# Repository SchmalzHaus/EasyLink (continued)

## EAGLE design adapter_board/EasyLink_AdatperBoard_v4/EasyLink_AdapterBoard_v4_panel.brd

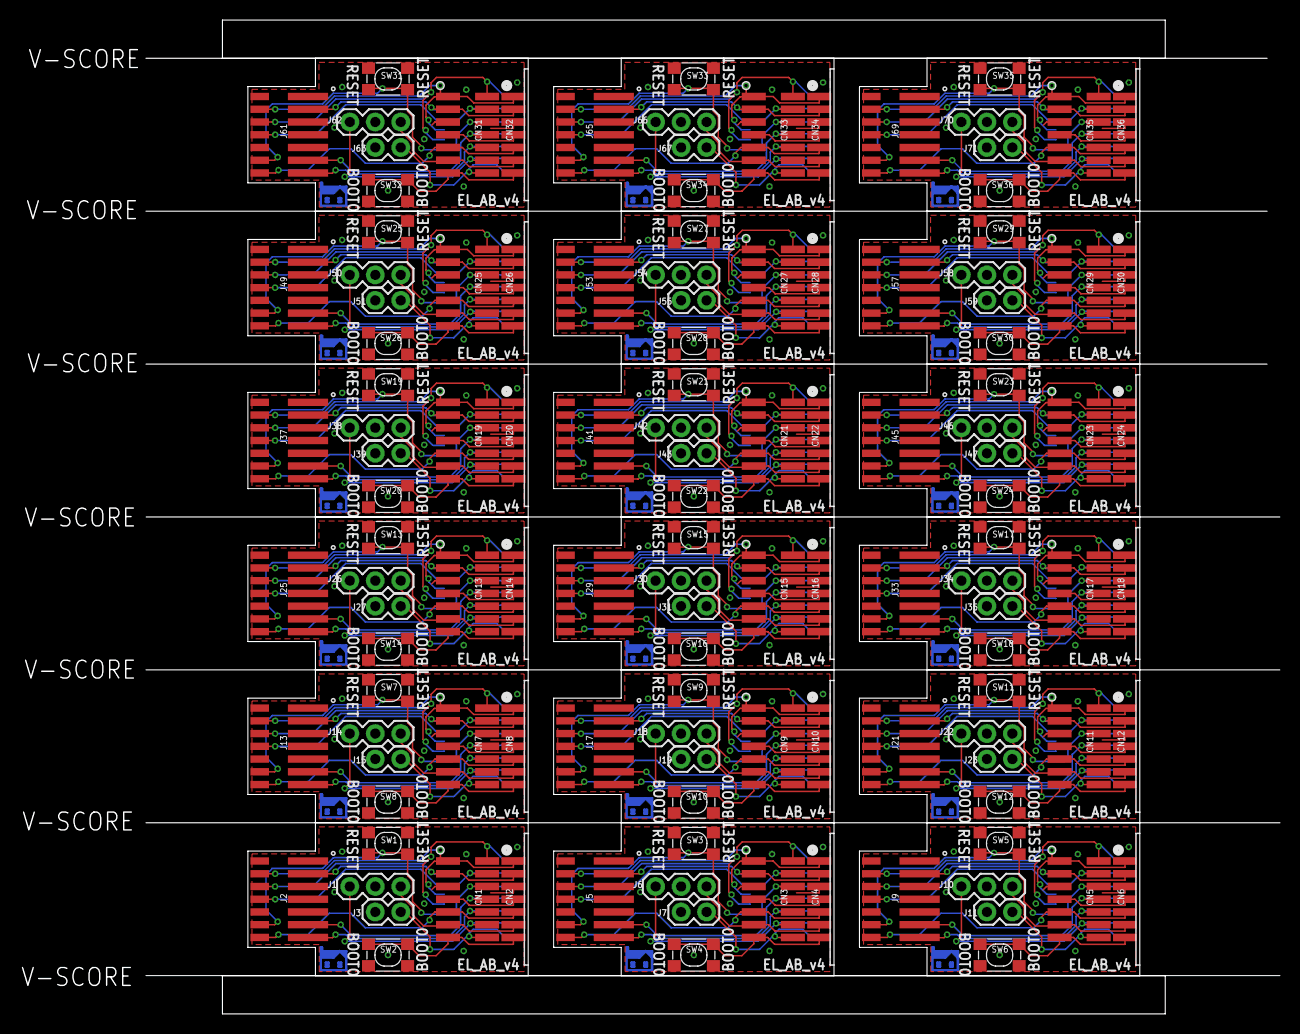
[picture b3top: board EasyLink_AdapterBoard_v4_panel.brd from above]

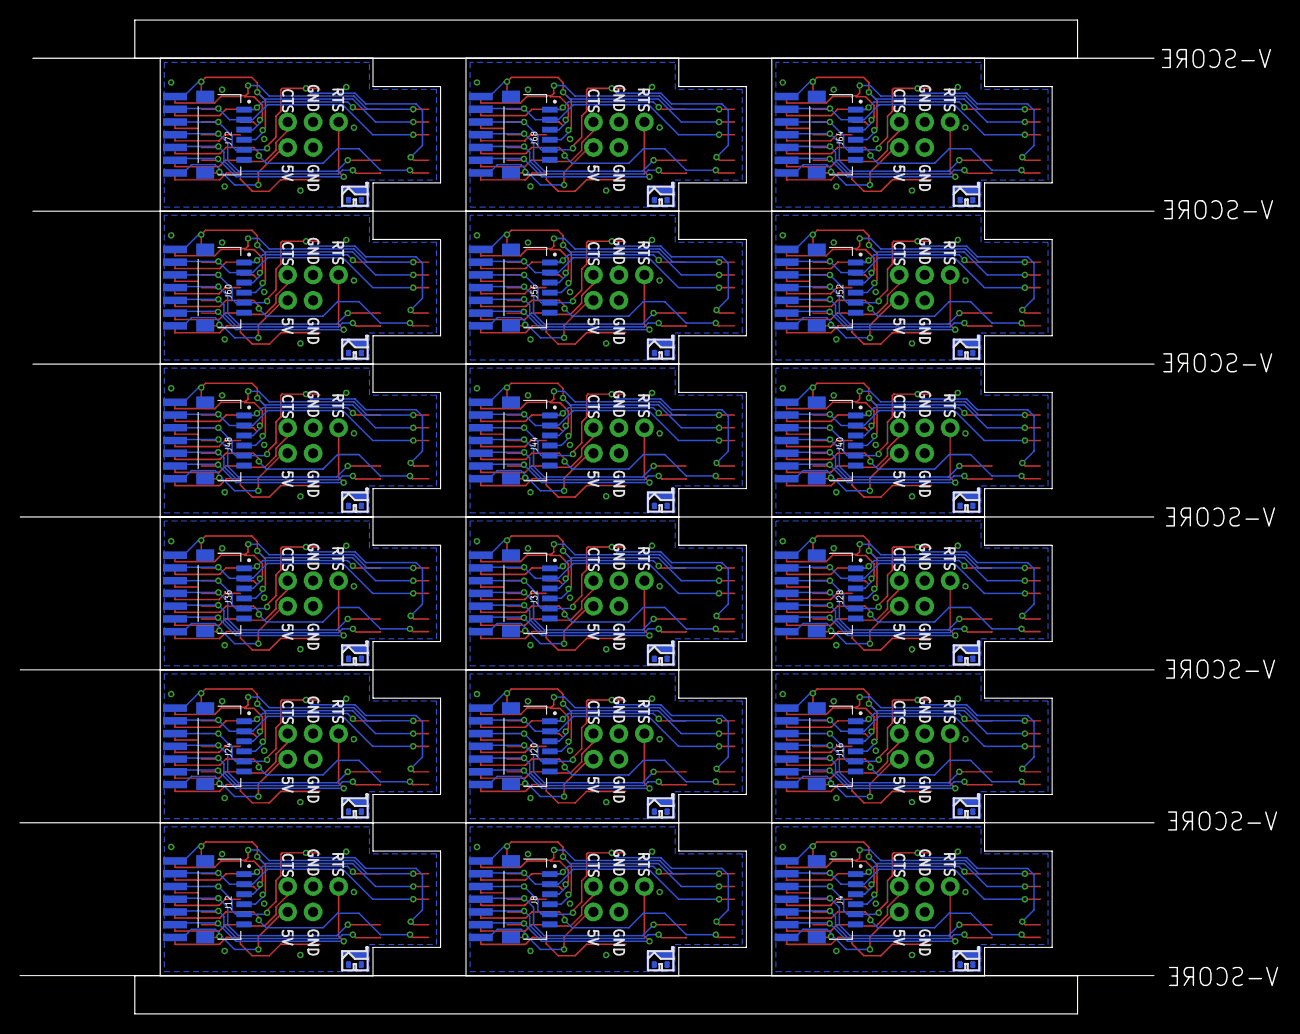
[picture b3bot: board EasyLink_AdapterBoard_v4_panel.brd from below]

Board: 2 copper layers, 113.0 x 99.1 mm, 162 parts (36 on the bottom side), 234 nets.

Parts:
CN1, CN3, CN5, CN7, CN9, CN11, CN13, CN15, CN17, CN19, CN21, CN23, CN25, CN27, CN29, CN31, CN33, CN35: 2X7_DEBUG_HEADFER; 20021121_2X7_SMT_MALE
CN2, CN4, CN6, CN8, CN10, CN12, CN14, CN16, CN18, CN20, CN22, CN24, CN26, CN28, CN30, CN32, CN34, CN36: 2X7_DEBUG_HEADFEREDGE; 2X7_MALE_BOARD_STRADDLE
J1, J6, J10, J14, J18, J22, J26, J30, J34, J38, J42, J46, J50, J54, J58, J62, J66, J70: 1X03
J2, J5, J9, J13, J17, J21, J25, J29, J33, J37, J41, J45, J49, J53, J57, J61, J65, J69: FLE-107-01-XX-DVSTLINK; ST_LINK_V3_DIRECT
J3, J7, J11, J15, J19, J23, J27, J31, J35, J39, J43, J47, J51, J55, J59, J63, J67, J71: 1X02
J4, J8, J12, J16, J20, J24, J28, J32, J36, J40, J44, J48, J52, J56, J60, J64, J68, J72: SM06B-SRSS-TB(LF)(SN); JST_SM06B-SRSS-TB(LF)(SN)
SW1, SW2, SW3, SW4, SW5, SW6, SW7, SW8, SW9, SW10, SW11, SW12, SW13, SW14, SW15, SW16, SW17, SW18, SW19, SW20, SW21, SW22, SW23, SW24, SW25, SW26, SW27, SW28, SW29, SW30, SW31, SW32, SW33, SW34, SW35, SW36: DHT-4235A; SW4-SMD-4.2X3.2X2.5MM
U$1, U$2, U$3, U$4, U$5, U$6, U$7, U$8, U$9, U$10, U$11, U$12, U$13, U$14, U$15, U$16, U$17, U$18: SCHMALZHAUSSCHMALZHAUS_SMALL; SCHMALZHAUS_SMALL

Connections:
3V3_T_VCC: CN1.P$3, CN2.P$3, J2.3, J4.1
3V3_T_VCC1: CN3.P$3, CN4.P$3, J5.3, J8.1
3V3_T_VCC2: CN5.P$3, CN6.P$3, J9.3, J12.1
3V3_T_VCC3: CN7.P$3, CN8.P$3, J13.3, J16.1
3V3_T_VCC4: CN9.P$3, CN10.P$3, J17.3, J20.1
3V3_T_VCC5: CN11.P$3, CN12.P$3, J21.3, J24.1
3V3_T_VCC6: CN13.P$3, CN14.P$3, J25.3, J28.1
3V3_T_VCC7: CN15.P$3, CN16.P$3, J29.3, J32.1
3V3_T_VCC8: CN17.P$3, CN18.P$3, J33.3, J36.1
3V3_T_VCC9: CN19.P$3, CN20.P$3, J37.3, J40.1
3V3_T_VCC10: CN21.P$3, CN22.P$3, J41.3, J44.1
3V3_T_VCC11: CN23.P$3, CN24.P$3, J45.3, J48.1
3V3_T_VCC12: CN25.P$3, CN26.P$3, J49.3, J52.1
3V3_T_VCC13: CN27.P$3, CN28.P$3, J53.3, J56.1
3V3_T_VCC14: CN29.P$3, CN30.P$3, J57.3, J60.1
3V3_T_VCC15: CN31.P$3, CN32.P$3, J61.3, J64.1
3V3_T_VCC16: CN33.P$3, CN34.P$3, J65.3, J68.1
3V3_T_VCC17: CN35.P$3, CN36.P$3, J69.3, J72.1
5V: CN1.P$14, CN2.P$14, J3.1
5V1: CN3.P$14, CN4.P$14, J7.1
5V2: CN5.P$14, CN6.P$14, J11.1
5V3: CN7.P$14, CN8.P$14, J15.1
5V4: CN9.P$14, CN10.P$14, J19.1
5V5: CN11.P$14, CN12.P$14, J23.1
5V6: CN13.P$14, CN14.P$14, J27.1
5V7: CN15.P$14, CN16.P$14, J31.1
5V8: CN17.P$14, CN18.P$14, J35.1
5V9: CN19.P$14, CN20.P$14, J39.1
5V10: CN21.P$14, CN22.P$14, J43.1
5V11: CN23.P$14, CN24.P$14, J47.1
5V12: CN25.P$14, CN26.P$14, J51.1
5V13: CN27.P$14, CN28.P$14, J55.1
5V14: CN29.P$14, CN30.P$14, J59.1
5V15: CN31.P$14, CN32.P$14, J63.1
5V16: CN33.P$14, CN34.P$14, J67.1
5V17: CN35.P$14, CN36.P$14, J71.1
BOOT0: CN1.P$13, CN2.P$13, SW2.1, SW2.2
BOOT1: CN3.P$13, CN4.P$13, SW4.1, SW4.2
BOOT2: CN5.P$13, CN6.P$13, SW6.1, SW6.2
BOOT3: CN7.P$13, CN8.P$13, SW8.1, SW8.2
BOOT4: CN9.P$13, CN10.P$13, SW10.1, SW10.2
BOOT5: CN11.P$13, CN12.P$13, SW12.1, SW12.2
BOOT6: CN13.P$13, CN14.P$13, SW14.1, SW14.2
BOOT7: CN15.P$13, CN16.P$13, SW16.1, SW16.2
BOOT8: CN17.P$13, CN18.P$13, SW18.1, SW18.2
BOOT9: CN19.P$13, CN20.P$13, SW20.1, SW20.2
BOOT10: CN21.P$13, CN22.P$13, SW22.1, SW22.2
BOOT11: CN23.P$13, CN24.P$13, SW24.1, SW24.2
BOOT12: CN25.P$13, CN26.P$13, SW26.1, SW26.2
BOOT13: CN27.P$13, CN28.P$13, SW28.1, SW28.2
BOOT14: CN29.P$13, CN30.P$13, SW30.1, SW30.2
BOOT15: CN31.P$13, CN32.P$13, SW32.1, SW32.2
BOOT16: CN33.P$13, CN34.P$13, SW34.1, SW34.2
BOOT17: CN35.P$13, CN36.P$13, SW36.1, SW36.2
CTS: CN1.P$11, CN2.P$11, J1.3
CTS1: CN3.P$11, CN4.P$11, J6.3
CTS2: CN5.P$11, CN6.P$11, J10.3
CTS3: CN7.P$11, CN8.P$11, J14.3
CTS4: CN9.P$11, CN10.P$11, J18.3
CTS5: CN11.P$11, CN12.P$11, J22.3
CTS6: CN13.P$11, CN14.P$11, J26.3
CTS7: CN15.P$11, CN16.P$11, J30.3
CTS8: CN17.P$11, CN18.P$11, J34.3
CTS9: CN19.P$11, CN20.P$11, J38.3
CTS10: CN21.P$11, CN22.P$11, J42.3
CTS11: CN23.P$11, CN24.P$11, J46.3
CTS12: CN25.P$11, CN26.P$11, J50.3
CTS13: CN27.P$11, CN28.P$11, J54.3
CTS14: CN29.P$11, CN30.P$11, J58.3
CTS15: CN31.P$11, CN32.P$11, J62.3
CTS16: CN33.P$11, CN34.P$11, J66.3
CTS17: CN35.P$11, CN36.P$11, J70.3
GND: CN1.P$5, CN1.P$7, CN2.P$5, CN2.P$7, J1.2, J2.5, J2.7, J3.2, J4.6, J4.S1, J4.S2, SW1.3, SW1.4, SW2.3, SW2.4
GND1: CN3.P$5, CN3.P$7, CN4.P$5, CN4.P$7, J5.5, J5.7, J6.2, J7.2, J8.6, J8.S1, J8.S2, SW3.3, SW3.4, SW4.3, SW4.4
GND2: CN5.P$5, CN5.P$7, CN6.P$5, CN6.P$7, J9.5, J9.7, J10.2, J11.2, J12.6, J12.S1, J12.S2, SW5.3, SW5.4, SW6.3, SW6.4
GND3: CN7.P$5, CN7.P$7, CN8.P$5, CN8.P$7, J13.5, J13.7, J14.2, J15.2, J16.6, J16.S1, J16.S2, SW7.3, SW7.4, SW8.3, SW8.4
GND4: CN9.P$5, CN9.P$7, CN10.P$5, CN10.P$7, J17.5, J17.7, J18.2, J19.2, J20.6, J20.S1, J20.S2, SW9.3, SW9.4, SW10.3, SW10.4
GND5: CN11.P$5, CN11.P$7, CN12.P$5, CN12.P$7, J21.5, J21.7, J22.2, J23.2, J24.6, J24.S1, J24.S2, SW11.3, SW11.4, SW12.3, SW12.4
GND6: CN13.P$5, CN13.P$7, CN14.P$5, CN14.P$7, J25.5, J25.7, J26.2, J27.2, J28.6, J28.S1, J28.S2, SW13.3, SW13.4, SW14.3, SW14.4
GND7: CN15.P$5, CN15.P$7, CN16.P$5, CN16.P$7, J29.5, J29.7, J30.2, J31.2, J32.6, J32.S1, J32.S2, SW15.3, SW15.4, SW16.3, SW16.4
GND8: CN17.P$5, CN17.P$7, CN18.P$5, CN18.P$7, J33.5, J33.7, J34.2, J35.2, J36.6, J36.S1, J36.S2, SW17.3, SW17.4, SW18.3, SW18.4
GND9: CN19.P$5, CN19.P$7, CN20.P$5, CN20.P$7, J37.5, J37.7, J38.2, J39.2, J40.6, J40.S1, J40.S2, SW19.3, SW19.4, SW20.3, SW20.4
GND10: CN21.P$5, CN21.P$7, CN22.P$5, CN22.P$7, J41.5, J41.7, J42.2, J43.2, J44.6, J44.S1, J44.S2, SW21.3, SW21.4, SW22.3, SW22.4
GND11: CN23.P$5, CN23.P$7, CN24.P$5, CN24.P$7, J45.5, J45.7, J46.2, J47.2, J48.6, J48.S1, J48.S2, SW23.3, SW23.4, SW24.3, SW24.4
GND12: CN25.P$5, CN25.P$7, CN26.P$5, CN26.P$7, J49.5, J49.7, J50.2, J51.2, J52.6, J52.S1, J52.S2, SW25.3, SW25.4, SW26.3, SW26.4
GND13: CN27.P$5, CN27.P$7, CN28.P$5, CN28.P$7, J53.5, J53.7, J54.2, J55.2, J56.6, J56.S1, J56.S2, SW27.3, SW27.4, SW28.3, SW28.4
GND14: CN29.P$5, CN29.P$7, CN30.P$5, CN30.P$7, J57.5, J57.7, J58.2, J59.2, J60.6, J60.S1, J60.S2, SW29.3, SW29.4, SW30.3, SW30.4
GND15: CN31.P$5, CN31.P$7, CN32.P$5, CN32.P$7, J61.5, J61.7, J62.2, J63.2, J64.6, J64.S1, J64.S2, SW31.3, SW31.4, SW32.3, SW32.4
GND16: CN33.P$5, CN33.P$7, CN34.P$5, CN34.P$7, J65.5, J65.7, J66.2, J67.2, J68.6, J68.S1, J68.S2, SW33.3, SW33.4, SW34.3, SW34.4
GND17: CN35.P$5, CN35.P$7, CN36.P$5, CN36.P$7, J69.5, J69.7, J70.2, J71.2, J72.6, J72.S1, J72.S2, SW35.3, SW35.4, SW36.3, SW36.4
NRST: CN1.P$6, CN2.P$6, J2.12, J4.5, SW1.1, SW1.2
NRST1: CN3.P$6, CN4.P$6, J5.12, J8.5, SW3.1, SW3.2
NRST2: CN5.P$6, CN6.P$6, J9.12, J12.5, SW5.1, SW5.2
NRST3: CN7.P$6, CN8.P$6, J13.12, J16.5, SW7.1, SW7.2
NRST4: CN9.P$6, CN10.P$6, J17.12, J20.5, SW9.1, SW9.2
NRST5: CN11.P$6, CN12.P$6, J21.12, J24.5, SW11.1, SW11.2
NRST6: CN13.P$6, CN14.P$6, J25.12, J28.5, SW13.1, SW13.2
NRST7: CN15.P$6, CN16.P$6, J29.12, J32.5, SW15.1, SW15.2
NRST8: CN17.P$6, CN18.P$6, J33.12, J36.5, SW17.1, SW17.2
NRST9: CN19.P$6, CN20.P$6, J37.12, J40.5, SW19.1, SW19.2
NRST10: CN21.P$6, CN22.P$6, J41.12, J44.5, SW21.1, SW21.2
NRST11: CN23.P$6, CN24.P$6, J45.12, J48.5, SW23.1, SW23.2
NRST12: CN25.P$6, CN26.P$6, J49.12, J52.5, SW25.1, SW25.2
NRST13: CN27.P$6, CN28.P$6, J53.12, J56.5, SW27.1, SW27.2
NRST14: CN29.P$6, CN30.P$6, J57.12, J60.5, SW29.1, SW29.2
NRST15: CN31.P$6, CN32.P$6, J61.12, J64.5, SW31.1, SW31.2
NRST16: CN33.P$6, CN34.P$6, J65.12, J68.5, SW33.1, SW33.2
NRST17: CN35.P$6, CN36.P$6, J69.12, J72.5, SW35.1, SW35.2
RTS: CN1.P$12, CN2.P$12, J1.1
RTS1: CN3.P$12, CN4.P$12, J6.1
RTS2: CN5.P$12, CN6.P$12, J10.1
RTS3: CN7.P$12, CN8.P$12, J14.1
RTS4: CN9.P$12, CN10.P$12, J18.1
RTS5: CN11.P$12, CN12.P$12, J22.1
RTS6: CN13.P$12, CN14.P$12, J26.1
RTS7: CN15.P$12, CN16.P$12, J30.1
RTS8: CN17.P$12, CN18.P$12, J34.1
RTS9: CN19.P$12, CN20.P$12, J38.1
RTS10: CN21.P$12, CN22.P$12, J42.1
RTS11: CN23.P$12, CN24.P$12, J46.1
RTS12: CN25.P$12, CN26.P$12, J50.1
RTS13: CN27.P$12, CN28.P$12, J54.1
RTS14: CN29.P$12, CN30.P$12, J58.1
RTS15: CN31.P$12, CN32.P$12, J62.1
RTS16: CN33.P$12, CN34.P$12, J66.1
RTS17: CN35.P$12, CN36.P$12, J70.1
SWCLK: CN1.P$2, CN2.P$2, J2.6, J4.4
SWCLK1: CN3.P$2, CN4.P$2, J5.6, J8.4
SWCLK2: CN5.P$2, CN6.P$2, J9.6, J12.4
SWCLK3: CN7.P$2, CN8.P$2, J13.6, J16.4
SWCLK4: CN9.P$2, CN10.P$2, J17.6, J20.4
SWCLK5: CN11.P$2, CN12.P$2, J21.6, J24.4
SWCLK6: CN13.P$2, CN14.P$2, J25.6, J28.4
SWCLK7: CN15.P$2, CN16.P$2, J29.6, J32.4
SWCLK8: CN17.P$2, CN18.P$2, J33.6, J36.4
SWCLK9: CN19.P$2, CN20.P$2, J37.6, J40.4
SWCLK10: CN21.P$2, CN22.P$2, J41.6, J44.4
SWCLK11: CN23.P$2, CN24.P$2, J45.6, J48.4
SWCLK12: CN25.P$2, CN26.P$2, J49.6, J52.4
SWCLK13: CN27.P$2, CN28.P$2, J53.6, J56.4
SWCLK14: CN29.P$2, CN30.P$2, J57.6, J60.4
SWCLK15: CN31.P$2, CN32.P$2, J61.6, J64.4
SWCLK16: CN33.P$2, CN34.P$2, J65.6, J68.4
SWCLK17: CN35.P$2, CN36.P$2, J69.6, J72.4
SWDIO: CN1.P$1, CN2.P$1, J2.4, J4.3
SWDIO1: CN3.P$1, CN4.P$1, J5.4, J8.3
SWDIO2: CN5.P$1, CN6.P$1, J9.4, J12.3
SWDIO3: CN7.P$1, CN8.P$1, J13.4, J16.3
SWDIO4: CN9.P$1, CN10.P$1, J17.4, J20.3
SWDIO5: CN11.P$1, CN12.P$1, J21.4, J24.3
SWDIO6: CN13.P$1, CN14.P$1, J25.4, J28.3
SWDIO7: CN15.P$1, CN16.P$1, J29.4, J32.3
SWDIO8: CN17.P$1, CN18.P$1, J33.4, J36.3
SWDIO9: CN19.P$1, CN20.P$1, J37.4, J40.3
SWDIO10: CN21.P$1, CN22.P$1, J41.4, J44.3
SWDIO11: CN23.P$1, CN24.P$1, J45.4, J48.3
SWDIO12: CN25.P$1, CN26.P$1, J49.4, J52.3
SWDIO13: CN27.P$1, CN28.P$1, J53.4, J56.3
SWDIO14: CN29.P$1, CN30.P$1, J57.4, J60.3
SWDIO15: CN31.P$1, CN32.P$1, J61.4, J64.3
SWDIO16: CN33.P$1, CN34.P$1, J65.4, J68.3
SWDIO17: CN35.P$1, CN36.P$1, J69.4, J72.3
SWO: CN1.P$4, CN2.P$4, J2.8, J4.2
SWO1: CN3.P$4, CN4.P$4, J5.8, J8.2
SWO2: CN5.P$4, CN6.P$4, J9.8, J12.2
SWO3: CN7.P$4, CN8.P$4, J13.8, J16.2
SWO4: CN9.P$4, CN10.P$4, J17.8, J20.2
SWO5: CN11.P$4, CN12.P$4, J21.8, J24.2
SWO6: CN13.P$4, CN14.P$4, J25.8, J28.2
SWO7: CN15.P$4, CN16.P$4, J29.8, J32.2
SWO8: CN17.P$4, CN18.P$4, J33.8, J36.2
SWO9: CN19.P$4, CN20.P$4, J37.8, J40.2
SWO10: CN21.P$4, CN22.P$4, J41.8, J44.2
SWO11: CN23.P$4, CN24.P$4, J45.8, J48.2
SWO12: CN25.P$4, CN26.P$4, J49.8, J52.2
SWO13: CN27.P$4, CN28.P$4, J53.8, J56.2
SWO14: CN29.P$4, CN30.P$4, J57.8, J60.2
SWO15: CN31.P$4, CN32.P$4, J61.8, J64.2
SWO16: CN33.P$4, CN34.P$4, J65.8, J68.2
SWO17: CN35.P$4, CN36.P$4, J69.8, J72.2
T_GND: CN1.P$8, CN2.P$8, J2.11
T_GND1: CN3.P$8, CN4.P$8, J5.11
T_GND2: CN5.P$8, CN6.P$8, J9.11
T_GND3: CN7.P$8, CN8.P$8, J13.11
T_GND4: CN9.P$8, CN10.P$8, J17.11
T_GND5: CN11.P$8, CN12.P$8, J21.11
T_GND6: CN13.P$8, CN14.P$8, J25.11
T_GND7: CN15.P$8, CN16.P$8, J29.11
T_GND8: CN17.P$8, CN18.P$8, J33.11
T_GND9: CN19.P$8, CN20.P$8, J37.11
T_GND10: CN21.P$8, CN22.P$8, J41.11
T_GND11: CN23.P$8, CN24.P$8, J45.11
T_GND12: CN25.P$8, CN26.P$8, J49.11
T_GND13: CN27.P$8, CN28.P$8, J53.11
T_GND14: CN29.P$8, CN30.P$8, J57.11
T_GND15: CN31.P$8, CN32.P$8, J61.11
T_GND16: CN33.P$8, CN34.P$8, J65.11
T_GND17: CN35.P$8, CN36.P$8, J69.11
VCP_RX_T_TX: CN1.P$9, CN2.P$9, J2.14
VCP_RX_T_TX1: CN3.P$9, CN4.P$9, J5.14
VCP_RX_T_TX2: CN5.P$9, CN6.P$9, J9.14
VCP_RX_T_TX3: CN7.P$9, CN8.P$9, J13.14
VCP_RX_T_TX4: CN9.P$9, CN10.P$9, J17.14
VCP_RX_T_TX5: CN11.P$9, CN12.P$9, J21.14
VCP_RX_T_TX6: CN13.P$9, CN14.P$9, J25.14
VCP_RX_T_TX7: CN15.P$9, CN16.P$9, J29.14
VCP_RX_T_TX8: CN17.P$9, CN18.P$9, J33.14
VCP_RX_T_TX9: CN19.P$9, CN20.P$9, J37.14
VCP_RX_T_TX10: CN21.P$9, CN22.P$9, J41.14
VCP_RX_T_TX11: CN23.P$9, CN24.P$9, J45.14
VCP_RX_T_TX12: CN25.P$9, CN26.P$9, J49.14
VCP_RX_T_TX13: CN27.P$9, CN28.P$9, J53.14
VCP_RX_T_TX14: CN29.P$9, CN30.P$9, J57.14
VCP_RX_T_TX15: CN31.P$9, CN32.P$9, J61.14
VCP_RX_T_TX16: CN33.P$9, CN34.P$9, J65.14
VCP_RX_T_TX17: CN35.P$9, CN36.P$9, J69.14
VCP_TX_T_RX: CN1.P$10, CN2.P$10, J2.13
VCP_TX_T_RX1: CN3.P$10, CN4.P$10, J5.13
VCP_TX_T_RX2: CN5.P$10, CN6.P$10, J9.13
VCP_TX_T_RX3: CN7.P$10, CN8.P$10, J13.13
VCP_TX_T_RX4: CN9.P$10, CN10.P$10, J17.13
VCP_TX_T_RX5: CN11.P$10, CN12.P$10, J21.13
VCP_TX_T_RX6: CN13.P$10, CN14.P$10, J25.13
VCP_TX_T_RX7: CN15.P$10, CN16.P$10, J29.13
VCP_TX_T_RX8: CN17.P$10, CN18.P$10, J33.13
VCP_TX_T_RX9: CN19.P$10, CN20.P$10, J37.13
VCP_TX_T_RX10: CN21.P$10, CN22.P$10, J41.13
VCP_TX_T_RX11: CN23.P$10, CN24.P$10, J45.13
VCP_TX_T_RX12: CN25.P$10, CN26.P$10, J49.13
VCP_TX_T_RX13: CN27.P$10, CN28.P$10, J53.13
VCP_TX_T_RX14: CN29.P$10, CN30.P$10, J57.13
VCP_TX_T_RX15: CN31.P$10, CN32.P$10, J61.13
VCP_TX_T_RX16: CN33.P$10, CN34.P$10, J65.13
VCP_TX_T_RX17: CN35.P$10, CN36.P$10, J69.13

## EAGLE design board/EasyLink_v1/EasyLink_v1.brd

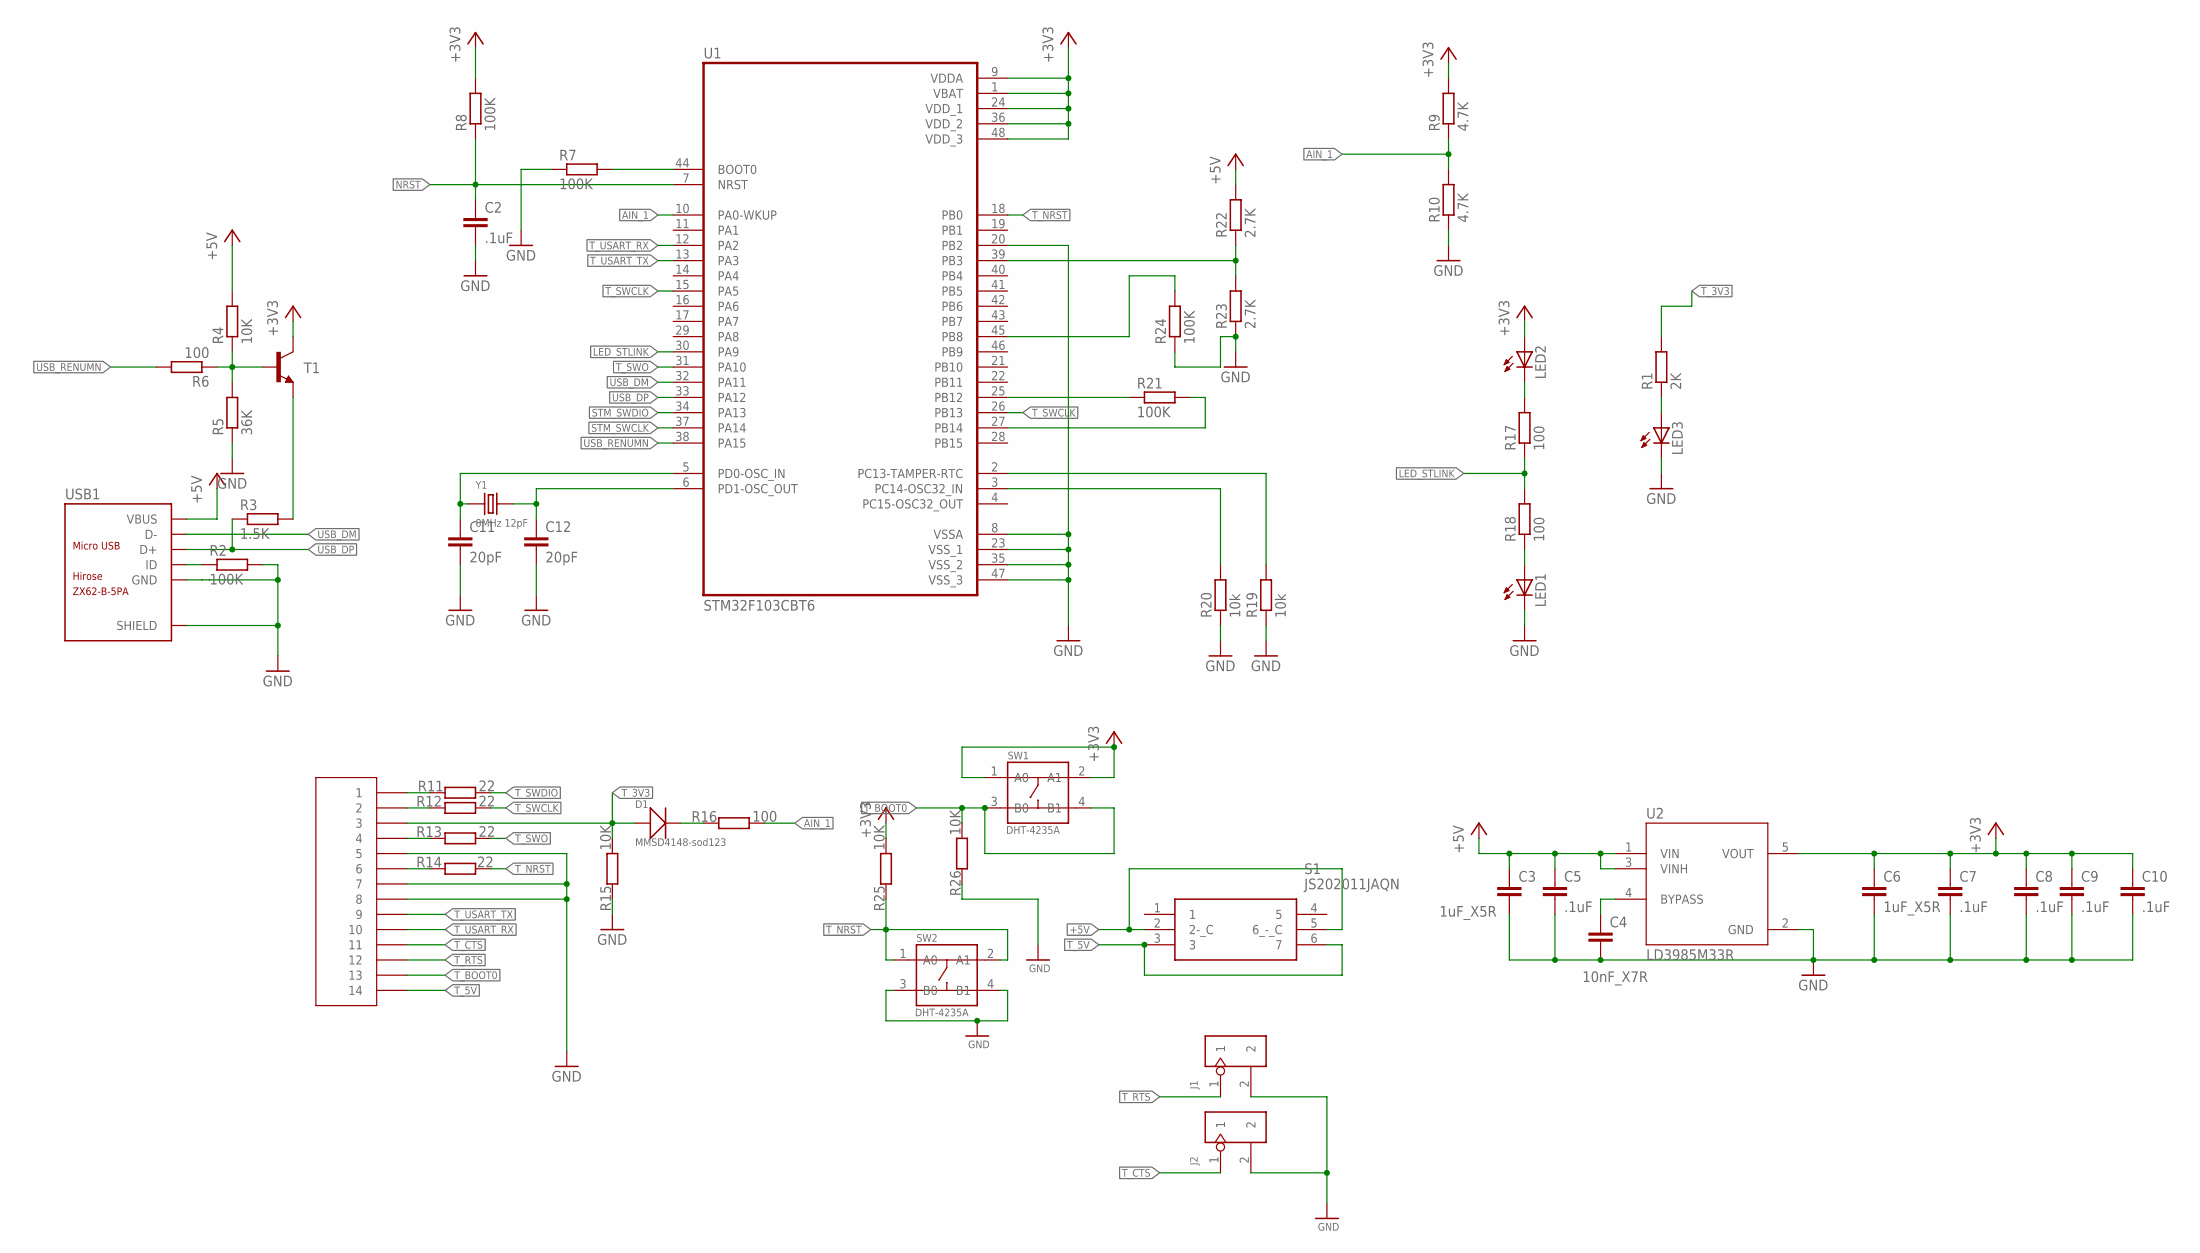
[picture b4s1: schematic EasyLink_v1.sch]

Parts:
C2, C5, C7, C8, C9, C10: .1uF; C0603
C3, C6: 1uF_X5R; C0603
C4: 10nF_X7R; C0603
C11, C12: 20pF; C0603
CN1: 2X7_DEBUG_HEADFER; 20021121_2X7_SMT_MALE
D1: MMSD4148-sod123; SOD-123
J1, J2: DIP-BLACK-JUMPER; H2-2.54
LED1, LED2, LED3: LED_ESML0603; LED_SML0603
R1: 2K; R0603
R2, R7, R8, R21, R24: 100K; R0603
R3: 1.5K; R0603
R4, R15, R25, R26: 10K; R0603
R5: 36K; R0603
R6, R16, R17, R18: 100; R0603
R9, R10: 4.7K; R0603
R11, R12, R13, R14: 22; R0603
R19, R20: 10k; R0603
R22, R23: 2.7K; R0603
S1: JS202011JAQN
SW1, SW2: DHT-4235A; SW4-SMD-4.2X3.2X2.5MM
T1: BCF30-NPN-SOT23-BEC; SOT23-BEC
U1: STM32F103CBT6; QFP50P900X900X160-48N
U2: LD3985M33R; SOT95P280X145-5N
USB1: ZX62-B-5PA; MICRO-USB5+6P-SMD-0.65-AB
Y1: 8MHz 12pF; X2-SMD-5.0X3.2X1.3MM

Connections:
+3V3: C6.1, C7.1, C8.1, C9.1, C10.1, LED2.A, R8.2, R9.2, R25.2, SW1.1 (A0), SW1.2 (A1), T1.C, U1.1 (VBAT), U1.9 (VDDA), U1.24 (VDD_1), U1.36 (VDD_2), U1.48 (VDD_3), U2.5 (VOUT)
+5V: C3.1, C5.1, R4.2, R22.2, S1.2 (2-_C), S1.5 (6_-_C), U2.1 (VIN), U2.3 (VINH), USB1.1 (VBUS)
AIN_1: R9.1, R10.2, R16.2, U1.10 (PA0-WKUP)
GND: C2.2, C3.2, C4.2, C5.2, C6.2, C7.2, C8.2, C9.2, C10.2, C11.2, C12.2, CN1.P$5 (5), CN1.P$7 (7), CN1.P$8 (8), J1.2, J2.2, LED1.C, LED3.C, R2.2, R5.1, R7.1, R10.1, R15.1, R19.1, R20.1, R23.1, R24.1, R26.1, SW2.3 (B0), SW2.4 (B1), U1.8 (VSSA), U1.20 (PB2), U1.23 (VSS_1), U1.35 (VSS_2), U1.47 (VSS_3), U2.2 (GND), USB1.5 (GND), USB1.P1 (SHIELD), USB1.P2 (SHIELD), USB1.P3 (SHIELD), USB1.P4 (SHIELD), USB1.P5 (SHIELD), USB1.P6 (SHIELD)
LED_STLINK: R17.1, R18.2, U1.30 (PA9)
unnamed: R3.2, T1.E
unnamed: CN1.P$1 (1), R11.1
unnamed: CN1.P$2 (2), R12.1
unnamed: CN1.P$4 (4), R13.1
unnamed: CN1.P$6 (6), R14.1
unnamed: R7.2, U1.44 (BOOT0)
unnamed: R2.1, USB1.4 (ID)
unnamed: D1.-, R16.1
unnamed: LED1.A, R18.1
unnamed: R4.1, R5.2, R6.1, T1.B
unnamed: LED2.C, R17.2
unnamed: R21.2, U1.27 (PB14)
unnamed: C4.1, U2.4 (BYPASS)
unnamed: LED3.A, R1.1
unnamed: R19.2, U1.2 (PC13-TAMPER-RTC)
unnamed: C11.1, U1.5 (PD0-OSC_IN), Y1.1
unnamed: C12.1, U1.6 (PD1-OSC_OUT), Y1.2
unnamed: R20.2, U1.3 (PC14-OSC32_IN)
unnamed: R24.2, U1.45 (PB8)
unnamed: R22.1, R23.2, U1.39 (PB3)
NRST: C2.1, R8.1, U1.7 (NRST)
STM_SWCLK: U1.37 (PA14)
STM_SWDIO: U1.34 (PA13)
T_3V3: CN1.P$3 (3), D1.+, R1.2, R15.2
T_5V: CN1.P$14 (14), S1.3, S1.6 (7)
T_BOOT0: CN1.P$13 (13), R26.2, SW1.3 (B0), SW1.4 (B1)
T_CTS: CN1.P$11 (11), J2.1
T_NRST: R14.2, R25.1, SW2.1 (A0), SW2.2 (A1), U1.18 (PB0)
T_RTS: CN1.P$12 (12), J1.1
T_SWCLK: R12.2, U1.15 (PA5), U1.26 (PB13)
T_SWDIO: R11.2, R21.1, U1.25 (PB12)
T_SWO: R13.2, U1.31 (PA10)
T_USART_RX: CN1.P$10 (10), U1.12 (PA2)
T_USART_TX: CN1.P$9 (9), U1.13 (PA3)
USB_DM: U1.32 (PA11), USB1.2 (D-)
USB_DP: R3.1, U1.33 (PA12), USB1.3 (D+)
USB_RENUMN: R6.2, U1.38 (PA15)

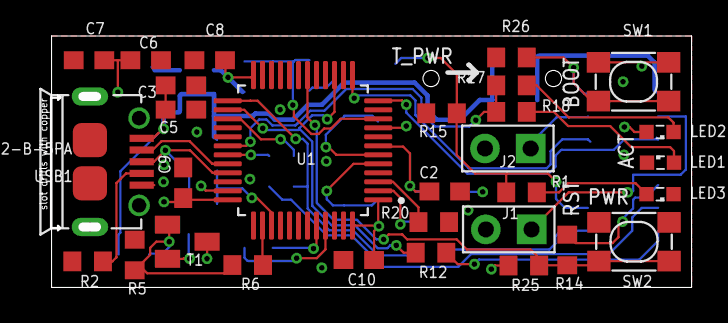
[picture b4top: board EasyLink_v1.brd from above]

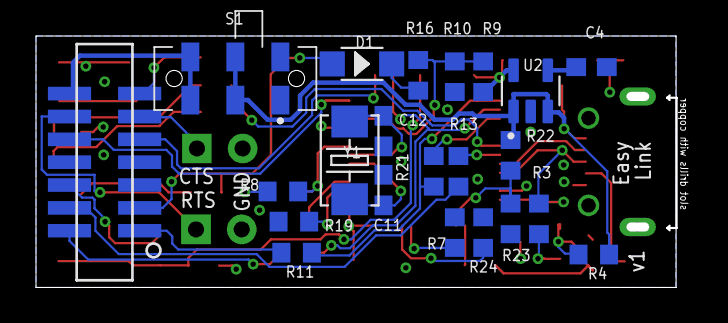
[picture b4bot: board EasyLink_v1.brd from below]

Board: 4 copper layers, 35.6 x 14.0 mm, 52 parts (22 on the bottom side), 40 nets.

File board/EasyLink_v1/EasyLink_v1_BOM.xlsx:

EasyLink v1
Designator | Quantity | Description | Part Number | DigiKey Part Number | Package
U1 | 1 | IC MCU 32BIT 128KB FLASH 48LQFP | STM32F103CBT6TR | 497-17380-1-ND | 48LQFP | MCU
USB1 | 1 | CONN RCPT USB2.0 MICRO B SMD R/A | ZX62-B-5PA(33) | H125270CT-ND |  | USB MicroB
CN1 | 1 | CONN HEADER SMD 14POS 1.27MM | 20021121-00014T4LF | 609-3730-ND |  | CSI debug/programming male header
U2 | 1 | IC REG LINEAR 3.3V 150MA SOT23-5 | LD3985M33R | 497-3504-1-ND | SOD23-5 | 3.3V power regulator
LED1 | 1 | LED RED DIFFUSED 0603 SMD | LS L29K-G1H2-1-Z | 475-3124-1-ND | 0603 | ST-Link LED
LED3 | 1 | LED YELLOW DIFFUSED 0603 SMD | LY L29K-J1K2-26-Z | 475-2794-1-ND | 0603 | 3.3V target power LED
LED2 | 1 | LED GREEN DIFFUSED 0603 SMD | LG L29K-F2J1-24-Z | 475-3118-1-ND | 0603 | ST-Link LED
S1 | 1 | Slide Switch DPDT Surface Mount, Right Angle | JS202011JAQN | CKN10722CT-ND |  | 5V power to target switch
SW1,SW2 | 2 | SWITCH TACTILE SPST-NO 0.05A 12V | TL3365AF180QG | EG5384CT-ND |  | Reset switch and boot switch
Y1 | 1 | CRYSTAL 8.0000MHZ 12PF SMD | CX5032GB08000H0HPQZ1 | 1253-1373-1-ND |  | 8MHz crystal
T1 | 1 | TRANS NPN 40V 0.2A SOT23 | MMBT3904,215 | 1727-4044-1-ND | SOT23 | USB Reenumeration transistor
D1 | 1 | DIODE GEN PURP 100V 200MA SOD123 | MMSD4148T1G | MMSD4148T1GOSCT-ND | SOD123 | voltage measurement diode
C2,C5,C7,C8,C9,C10 | 6 |  |  |  | 0603 | .1uF cap
R9,R10 | 2 |  |  |  | 0603 | 4.7K resistor
C11, C12 | 2 | CAP CER 20PF 50V C0G/NPO 0603 | CC0603JRNPO9BN200 | 311-1424-1-ND | 0603 | 8MHz cyrstal load caps
R11,R12,R13,R14 | 4 |  |  |  | 0603 | 22 ohm
C3,C6 | 2 | CAP CER 1UF 10V X5R 0603 | CL10A105KP8NNNC | 1276-1182-1-ND | 0603
C4 | 1 | CAP CER 0603 10NF 16V X7R 10% | C0603C103K4RECAUTO | 399-17880-1-ND | 0603
R4,R19,R20,R25,R26,R15 |  |  |  |  |  | 10 K ohm
R6,R17,R19,R1,R16 |  |  |  |  |  | 100 ohm
R3 |  |  |  |  |  | 1.5 K ohm
R2,R7,R8,R24,R21 |  |  |  |  |  | 100K ohm
R5 |  |  |  |  |  | 36K ohm
R22,R23 |  |  |  |  |  | 2.7K ohm
 | 0 | CONN HEADER VERT 14POS 1.27MM | 20021111-00014T4LF | 609-3714-ND |  | Through hole (across board edge) 2x7 debug header (must make board 0.8mm thick)
